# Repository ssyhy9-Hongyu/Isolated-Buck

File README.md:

# Isolated-Buck
50W Isolated Buck Converter (Two Switch Foward Converter) Project

Project Date: Sept.2022 - Jan.2023
Location: Nottingham UK  
People: Hongyu Yan, Pengyuan Shu, Jasleen Kaur, Jed Gawan

System block diagram:

Photo of the converter:

PCB Design Schematic (Converter Board):

PCB Design Schematic (Control Board):

PCB Layout (Converter Board):

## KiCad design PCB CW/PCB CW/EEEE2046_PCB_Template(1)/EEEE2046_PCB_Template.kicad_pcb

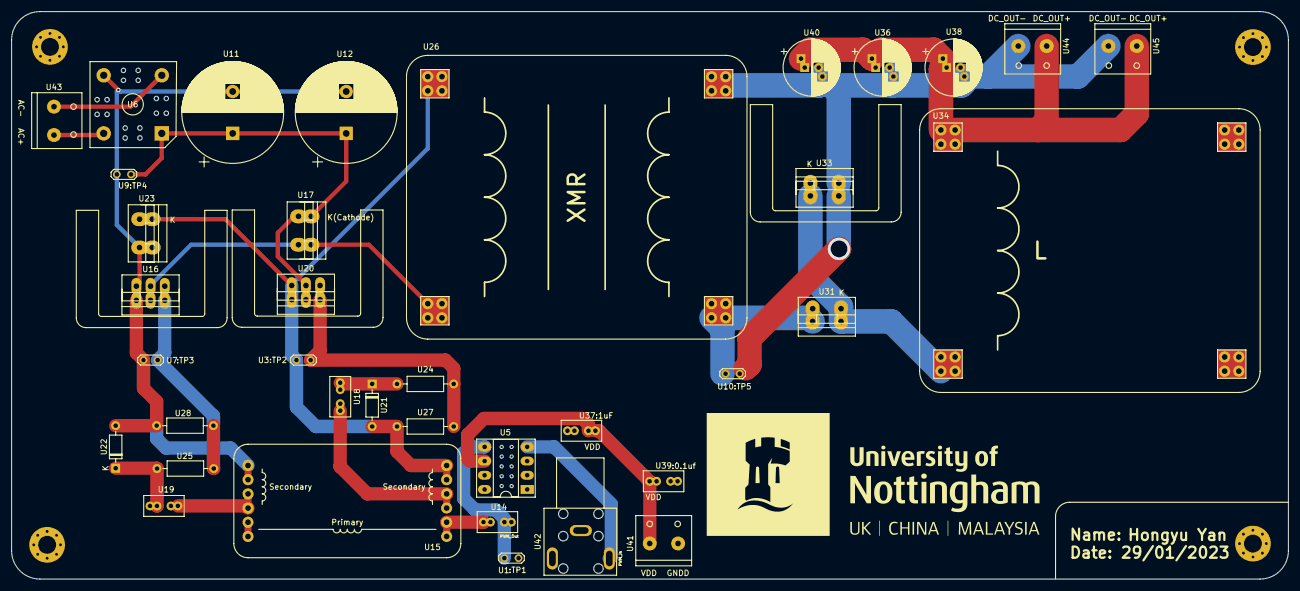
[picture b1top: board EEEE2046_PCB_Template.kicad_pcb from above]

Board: 2 copper layers, 228.6 x 101.6 mm, 44 parts (0 on the bottom side), 21 nets.

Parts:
H2, H2#2, H4, H4#2: Mount; MountingHole_3.2mm_M3_Pad_Via
U1: TP_PWM_Out; TestPoint_2Pads_Pitch2.54mm_Drill0.8mm
U2-Mosfet1, U3-Diode1, U4-Diode1: TO220_Heatsink
U3: TP_Q1_Gate; TestPoint_2Pads_Pitch2.54mm_Drill0.8mm
U5: TC4425AVPA; DIP-8_W7.62mm_Socket_LongPads
U6: VS-KBPC606PBF; Diode_Bridge_Vishay_KBPC6
U7: TP_Q2_Gate; TestPoint_2Pads_Pitch2.54mm_Drill0.8mm
U9: TP_DC_Link; TestPoint_2Pads_Pitch2.54mm_Drill0.8mm
U10: TP_Trans_Out; TestPoint_2Pads_Pitch2.54mm_Drill0.8mm
U11, U12: ECA2AM102; CP_Radial_D18.0mm_P7.50mm
U14, U18, U19: F; C_Rect_L7.0mm_W3.5mm_P2.50mm_P5.00mm
U15: Toroid-Transformer_1P_2S
U16, U20: IRFI530NPbF; TO-220FPAB
U17, U23, U31, U33: BYV25FX-600; SOD113
U21, U22: V; D_DO-35_SOD27_P7.62mm_Horizontal
U24, U25, U27, U28: R; R_Axial_DIN0207_L6.3mm_D2.5mm_P10.16mm_Horizontal
U26: ETD_34-Transformer_1P_1S; ETD_34-XMR
U34: H; ETD_34-L
U36, U38, U40: F; CP_Radial_D10.0mm_P2.50mm_P5.00mm
U37: 1uF; C_Rect_L7.0mm_W3.5mm_P2.50mm_P5.00mm
U39: 0.1 uF; C_Rect_L7.0mm_W3.5mm_P2.50mm_P5.00mm
U41: PWM_Power; 2wayTerminalBlock
U42: PWM_Input; LP-0841-3B-05A
U43: AC_Power; 2wayTerminalBlock
U44, U45: Converter_Out; 2wayTerminalBlock

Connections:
/Converter_Out(+): U34.1, U36.1, U38.1, U40.1, U44.1, U45.1
/Converter_Out(-): U10.2, U26.3 (SA), U33.2 (A), U36.2, U38.2, U40.2, U44.2, U45.2
/PWM_COM_A: U3.2, U15.4 (SB), U20.3 (S), U21.2 (A), U23.1 (K), U26.1 (AA), U27.1
/PWM_COM_B: U6.3 (-), U7.2, U9.2, U11.2, U12.2, U15.6 (SD), U16.3 (S), U22.2 (A), U23.2 (A), U28.1
/PWM_Input: U5.4 (IN_B), U42.2
/PWM_OUT_A: U3.1, U20.1 (G), U24.1, U27.2
/PWM_OUT_B: U7.1, U16.1 (G), U25.1, U28.2
/PWM_Out: U1.1, U5.5 (OUT_B), U14.2
/Rectifier_DC(+): U6.1 (+), U9.1, U11.1, U12.1, U17.1 (K), U20.2 (D)
/Transformer_Out(+): U10.1, U26.4 (SB), U31.2 (A)
/VAC(+): U6.4, U43.2
/VAC(-): U6.2, U43.1
GNDD: U1.2, U5.3 (GND), U15.2 (AB), U37.2, U39.2, U41.2, U42.1
unnamed: U14.1, U15.1 (AA)
unnamed: U15.3 (SA), U18.2
unnamed: U15.5 (SC), U19.2
unnamed: U16.2 (D), U17.2 (A), U26.2 (AB)
unnamed: U18.1, U21.1 (K), U24.2
unnamed: U19.1, U22.1 (K), U25.2
unnamed: U31.1 (K), U33.1 (K), U34.2
VDD: U5.6 (VDD), U37.1, U39.1, U41.1

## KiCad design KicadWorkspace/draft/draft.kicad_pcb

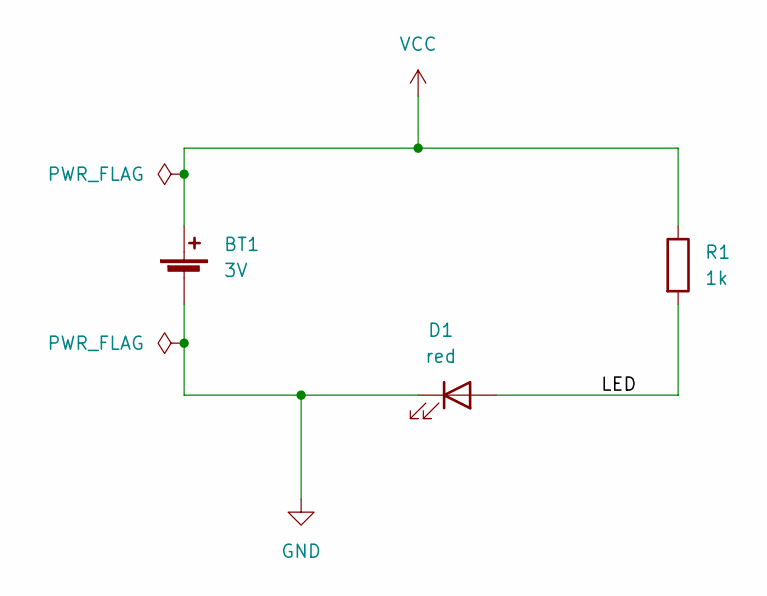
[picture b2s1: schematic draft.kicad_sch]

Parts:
BT1: 3V; Battery_Panasonic_CR1632-V1AN_Vertical_CircularHoles
D1: red; LED_D3.0mm
R1: 1k; R_Axial_DIN0309_L9.0mm_D3.2mm_P12.70mm_Horizontal

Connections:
/LED: D1.2 (A), R1.2
GND: BT1.2 (-), D1.1 (K)
VCC: BT1.1 (+), R1.1

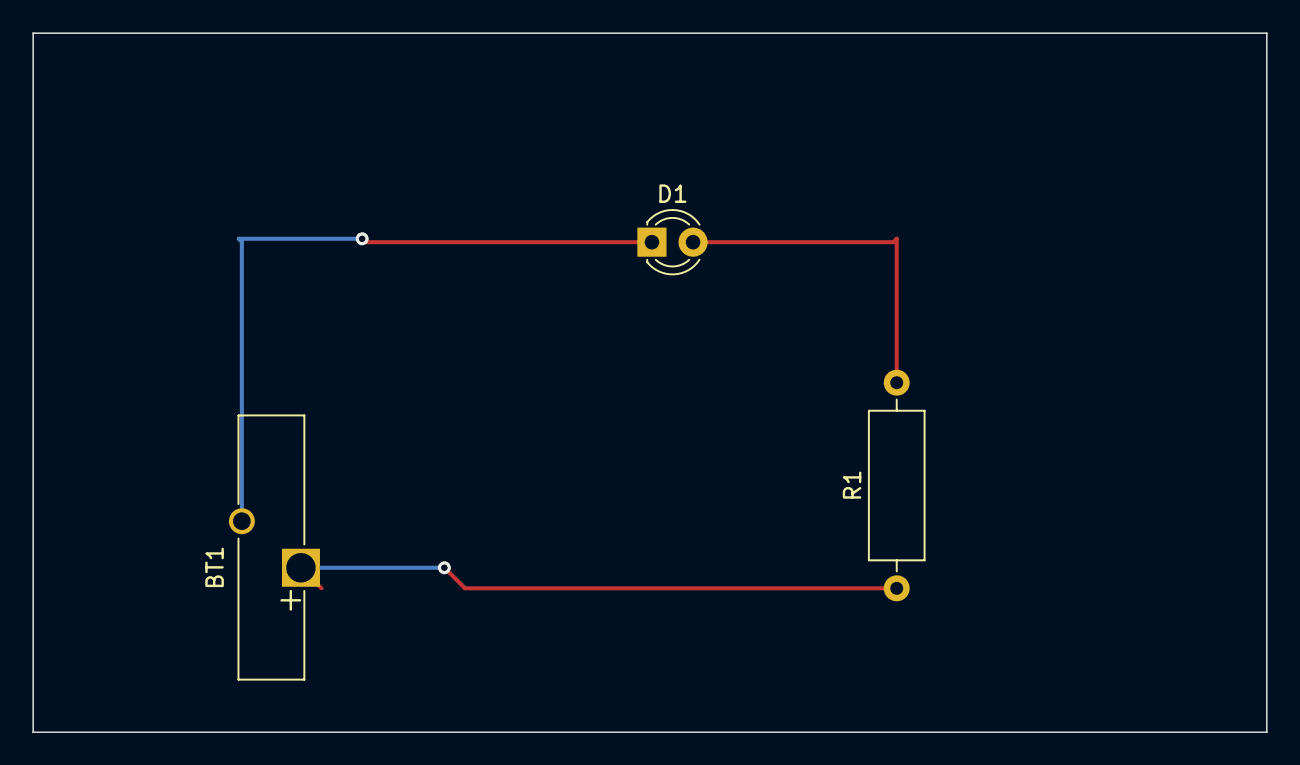
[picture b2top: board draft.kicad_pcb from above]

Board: 2 copper layers, 76.2 x 43.2 mm, 3 parts (0 on the bottom side), 3 nets.

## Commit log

2025-11-16 First Project Upload
